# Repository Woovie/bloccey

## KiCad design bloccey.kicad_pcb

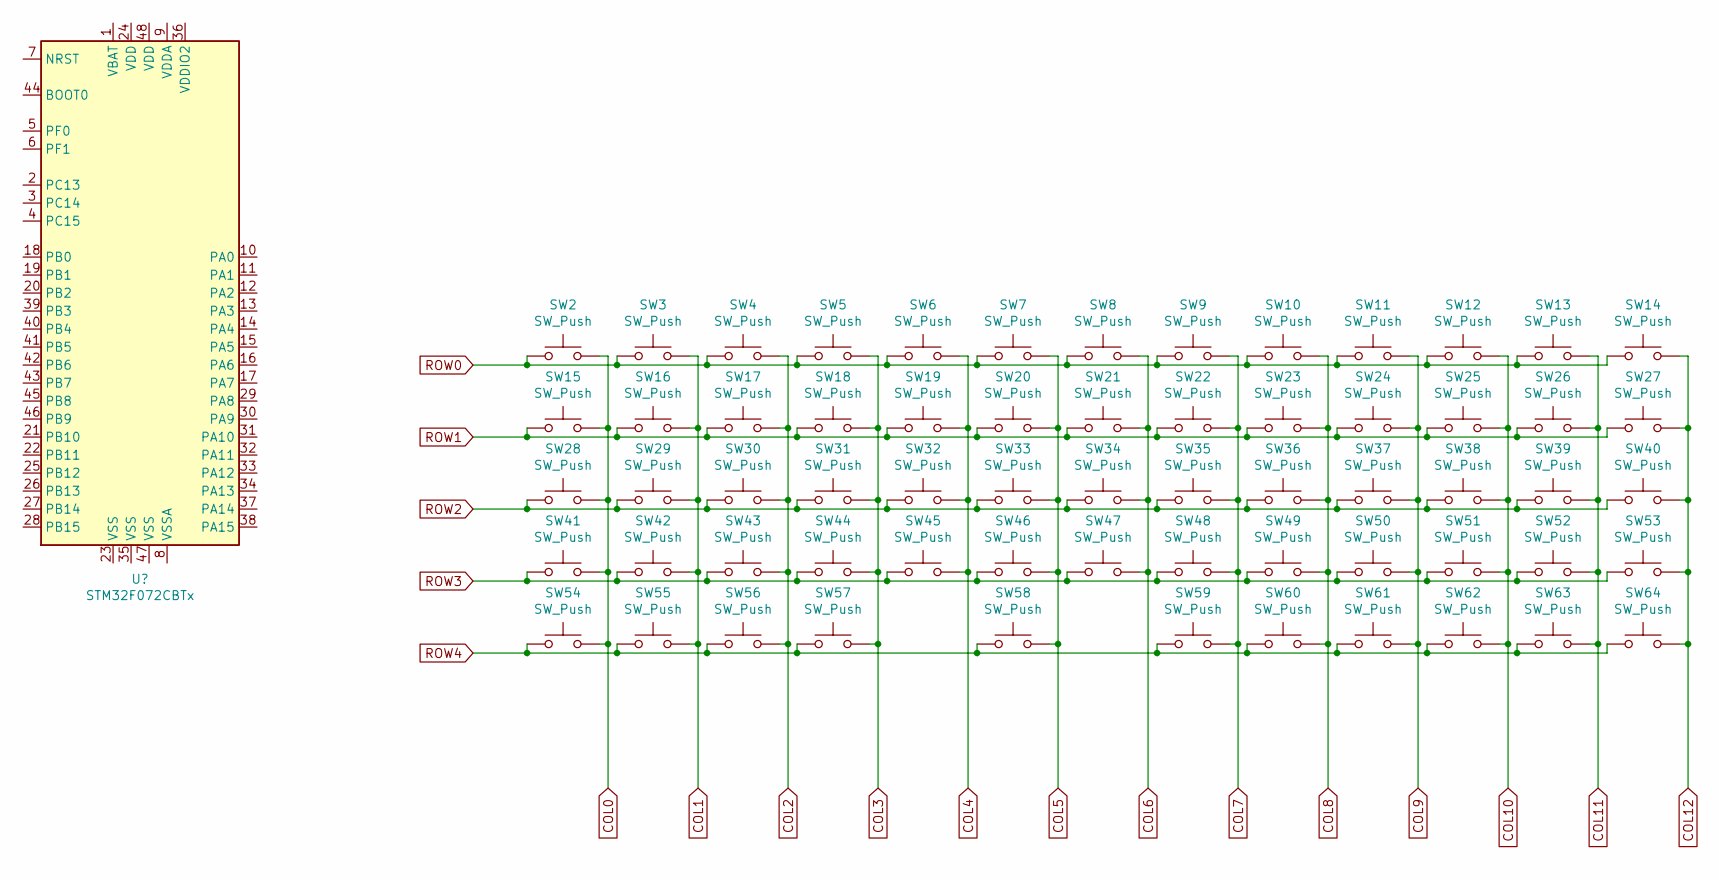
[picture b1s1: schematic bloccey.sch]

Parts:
SW2, SW3, SW4, SW5, SW6, SW7, SW8, SW9, SW10, SW11, SW12, SW13, SW14, SW15, SW16, SW17, SW18, SW19, SW20, SW21, SW22, SW23, SW24, SW25, SW26, SW27, SW28, SW29, SW30, SW31, SW32, SW33, SW34, SW35, SW36, SW37, SW38, SW39, SW40, SW41, SW42, SW43, SW44, SW45, SW46, SW47, SW48, SW49, SW50, SW51, SW52, SW53, SW54, SW55, SW56, SW57, SW58, SW59, SW60, SW61, SW62, SW63, SW64: SW_Push; PushButton_6x6mm_TH_Pretty

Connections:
COL0: SW2.2, SW15.2, SW28.2, SW41.2, SW54.2
COL1: SW3.2, SW16.2, SW29.2, SW42.2, SW55.2
COL2: SW4.2, SW17.2, SW30.2, SW43.2, SW56.2
COL3: SW5.2, SW18.2, SW31.2, SW44.2, SW57.2
COL4: SW6.2, SW19.2, SW32.2, SW45.2
COL5: SW7.2, SW20.2, SW33.2, SW46.2, SW58.2
COL6: SW8.2, SW21.2, SW34.2, SW47.2
COL7: SW9.2, SW22.2, SW35.2, SW48.2, SW59.2
COL8: SW10.2, SW23.2, SW36.2, SW49.2, SW60.2
COL9: SW11.2, SW24.2, SW37.2, SW50.2, SW61.2
COL10: SW12.2, SW25.2, SW38.2, SW51.2, SW62.2
COL11: SW13.2, SW26.2, SW39.2, SW52.2, SW63.2
COL12: SW14.2, SW27.2, SW40.2, SW53.2, SW64.2
ROW0: SW2.1, SW3.1, SW4.1, SW5.1, SW6.1, SW7.1, SW8.1, SW9.1, SW10.1, SW11.1, SW12.1, SW13.1, SW14.1
ROW1: SW15.1, SW16.1, SW17.1, SW18.1, SW19.1, SW20.1, SW21.1, SW22.1, SW23.1, SW24.1, SW25.1, SW26.1, SW27.1
ROW2: SW28.1, SW29.1, SW30.1, SW31.1, SW32.1, SW33.1, SW34.1, SW35.1, SW36.1, SW37.1, SW38.1, SW39.1, SW40.1
ROW3: SW41.1, SW42.1, SW43.1, SW44.1, SW45.1, SW46.1, SW47.1, SW48.1, SW49.1, SW50.1, SW51.1, SW52.1, SW53.1
ROW4: SW54.1, SW55.1, SW56.1, SW57.1, SW58.1, SW59.1, SW60.1, SW61.1, SW62.1, SW63.1, SW64.1

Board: 2 copper layers, 63 parts (0 on the bottom side), 18 nets, no tracks yet.

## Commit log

2019-07-11 Initial kicad project files
2019-07-11 Added submodules
2019-07-11 Initial switch placement, tables
2019-07-11 Start of PCB layout, finished sch
2019-07-11 Updated switch positions
2019-07-12 Switch to STM32, redo PCB
